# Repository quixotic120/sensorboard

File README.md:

Sense board - my layout (which is very close to orig tbh), orig by dc42 - his readme below. cc4.0-noncommercial license

OrmerodSensorBoard
==================

Here are the design files for my Z-height sensor board add-on to the RepRapPro Ormerod 3D printer. This board replaces the original IR sensor board used for Z-probing. It has the following advantages over the original:

1. It uses modulated infrared light, which makes it much less sensitive to ambient infrared such as is found in sunlight and in incandescent artificial light.
2. The sensor board is mounted on the hot end so that the sensor head is in-line with the nozzle in the x-direction. This makes it much less sensitive to variations in head sag.
3. The board includes the facility to mount the hot end connectors, eliminating the need for the original 6-pin connector. The new connectors are more reliable and more easily disassembled. In particular, the crimp receptacles can more easily be removed from the connector shell.
4. The board can accommodate three Cree LEDs to direct light on the work being printed. Alternatively, it can provide 12V power to an LED strip, or a constant-current supply to external LEDs.
5. The board includes provision for thermostatic control of the hot end fan. The fan is turned on when the hot end temperature exceeds approximately 42C, or when the board detects a hot end temperature measurement fault.
6. The board can also support an experimental ultrasonic sensor. This allows z-probing to be done anywhere on the bed. Due to variation in the speed of sound with temperature, the ultrasonic sensor is a little temperature-sensitive, but this can be compensated in the firmware.

Work is in progress to adapt the board for capacitive height sensing.

For assembly and usage instructions, please visit: http://miscsolutions.wordpress.com/assembling-and-using-the-eschertech-ormerod-hot-end-board/

I supply bare boards, kits of parts with all SMD components ready-mounted, and fully assembled boards. Contact me via the RepRap Ormerod forum at http://forums.reprap.org/list.php?340 by sending a personal message to dc42.

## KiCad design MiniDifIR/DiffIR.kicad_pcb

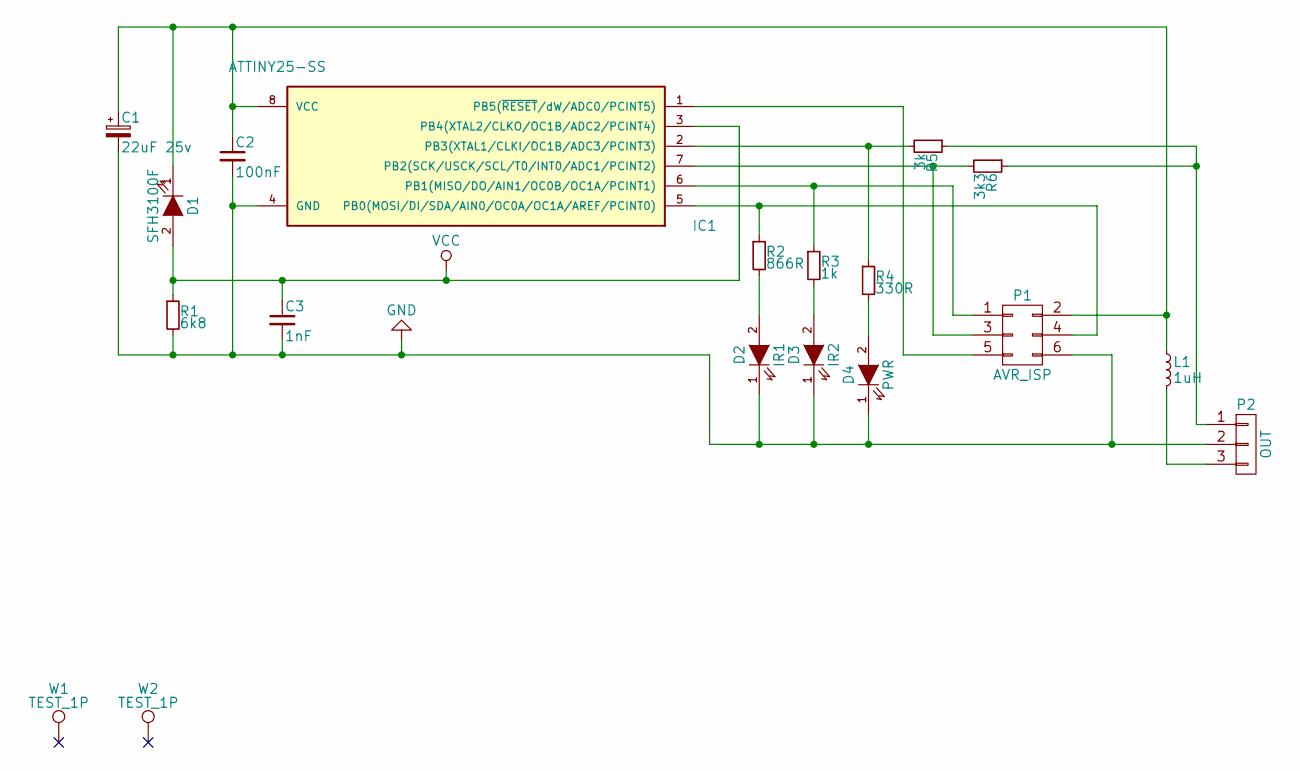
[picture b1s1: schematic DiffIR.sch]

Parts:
C1: 22uF 25v; c_elec_5x5.7
C2: 100nF; C_0805
C3: 1nF; C_0805
D1: SFH3100F; LED-5MM
D2: IR1; LED-5MM
D3: IR2; LED-5MM
D4: PWR; LED_0805
IC1: ATTINY25-SS; SOIC-8_3.9x4.9mm_Pitch1.27mm
L1: 1uH; C_0805
P1: AVR_ISP; Pin_Header_Straight_2x03
P2: OUT; Pin_Header_Straight_1x03
R1: 6k8; R_0805
R2: 866R; R_0805
R3: 1k; R_0805
R4: 330R; R_0805
R5: 3k; R_0805
R6: 3k3; R_0805
W1, W2: TEST_1P; MountingHole_3mm

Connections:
GND: C1.2, C2.2, C3.2, D2.1 (K), D3.1 (K), D4.1 (K), IC1.4 (GND), P1.6, P2.2, R1.2
unnamed: C1.1, C2.1, D1.1 (K), IC1.8 (VCC), L1.1, P1.2
unnamed: D2.2 (A), R2.2
unnamed: D3.2 (A), R3.2
unnamed: D4.2 (A), R4.2
unnamed: IC1.1 (PB5(~RESET~/dW/ADC0/PCINT5)), P1.5
unnamed: IC1.2 (PB3(XTAL1/CLKI/OC1B/ADC3/PCINT3)), R4.1, R5.2
unnamed: IC1.5 (PB0(MOSI/DI/SDA/AIN0/OC0A/OC1A/AREF/PCI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), P1.4, R2.1
unnamed: IC1.6 (PB1(MISO/DO/AIN1/OC0B/OC1A/PCINT1)), P1.1, R3.1
unnamed: IC1.7 (PB2(SCK/USCK/SCL/T0/INT0/ADC1/PCINT2)), P1.3, R6.2
unnamed: L1.2, P2.3
unnamed: P2.1, R5.1, R6.1
VCC: C3.1, D1.2 (A), IC1.3 (PB4(XTAL2/CLKO/OC1B/ADC2/PCINT4)), R1.1

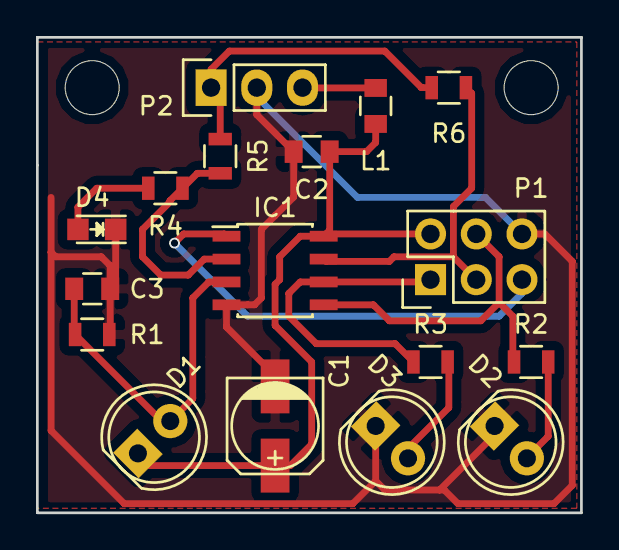
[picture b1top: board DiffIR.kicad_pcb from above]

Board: 2 copper layers, 30.2 x 26.4 mm, 19 parts (0 on the bottom side), 13 nets.

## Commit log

2016-03-25 dc42 diff optostop
    remix of dc42’s differential IR endstop
2016-03-27 thickened traces
2016-03-27 added renders
2016-05-14 diff IR
